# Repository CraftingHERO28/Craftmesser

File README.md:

# DIY Room Air Quality Monitor

I wanted to build a solid, reliable indoor air quality monitor to keep track of CO2 levels, temperature, and humidity in my room. A lot of cheap commercial monitors use estimated VOC sensors instead of actual optical sensors, so I decided to design my own board around an Arduino Nano and an NDIR MH-Z19B sensor.

## How it works & Hardware choices
The setup is built completely with through-hole (THT) components on socket headers so everything stays easy to solder and swap out if needed:

- **Arduino Nano v3.x** handling the logic.
- **MH-Z19B** for actual NDIR CO2 measurement.
- **DHT22 / AM2302** for temperature and humidity.
- **0.96" I2C OLED** for displaying live data.
- Decoupling caps (100nF ceramic & 100uF electrolytic) to smooth out voltage drops when the CO2 sensor warms up, plus a 10k pull-up for the DHT data line.

## Design notes & Things I ran into

- **Thermal Isolation:** The biggest challenge was keeping heat from the Arduino regulator and the CO2 sensor away from the temperature reading. I ended up placing the DHT22 at the far corner of the PCB away from major trace paths. 
- **Trace Routing:** I initially tried making decorative parallel power traces ("trace art"), but quickly realized it created routing clutter and unnecessary heat bridges toward the temp sensor. Going back to clean, single traces worked much better.
- **Edge Cuts:** I also experimented with slot cutouts on the PCB board outline (`Edge.Cuts`) for thermal isolation, but KiCad threw continuous DRC errors for open contours. Placing the sensor at the board edge using FR4's natural isolation turned out to be more than enough without messing with custom PCB millings.

## Total Cost
Total cost ended up around **€58 / ~$63 USD**, including component sourcing from Reichelt and getting 5 custom PCBs fabricated via JLCPCB (shipping included). Full component breakdown is available in the `BOM.csv` file.

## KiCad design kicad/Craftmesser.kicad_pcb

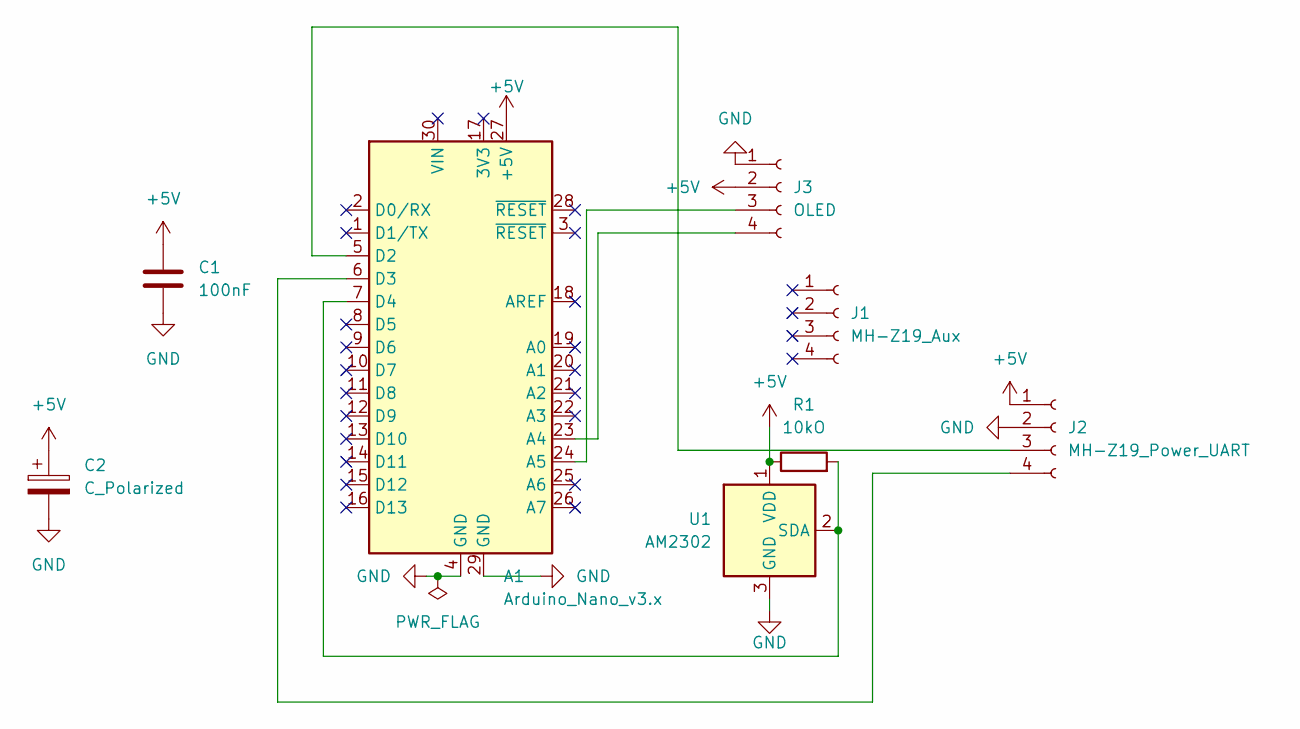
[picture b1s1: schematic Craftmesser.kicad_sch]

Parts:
A1: Arduino_Nano_v3.x; Arduino_Nano
C1: 100nF; C_Disc_D5.0mm_W2.5mm_P5.00mm
C2: C_Polarized; CP_Radial_D6.3mm_P2.50mm
J1: MH-Z19_Aux; PinHeader_1x04_P2.54mm_Vertical
J2: MH-Z19_Power_UART; PinHeader_1x04_P2.54mm_Vertical
J3: OLED; PinHeader_1x04_P2.54mm_Vertical
R1: 10kO; R_Axial_DIN0207_L6.3mm_D2.5mm_P7.62mm_Horizontal
U1: AM2302; ASAIR_AM2302_P2.54mm_Vertical

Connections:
+5V: A1.27 (+5V), C1.1, C2.1, J2.1, J3.2, R1.1, U1.1 (VDD)
GND: A1.4 (GND), A1.29 (GND), C1.2, C2.2, J2.2, J3.1, U1.3 (GND), U1.4 (GND)
unnamed: A1.23 (A4), J3.4
unnamed: A1.24 (A5), J3.3
unnamed: A1.5 (D2), J2.3
unnamed: A1.6 (D3), J2.4
unnamed: A1.7 (D4), R1.2, U1.2 (SDA)

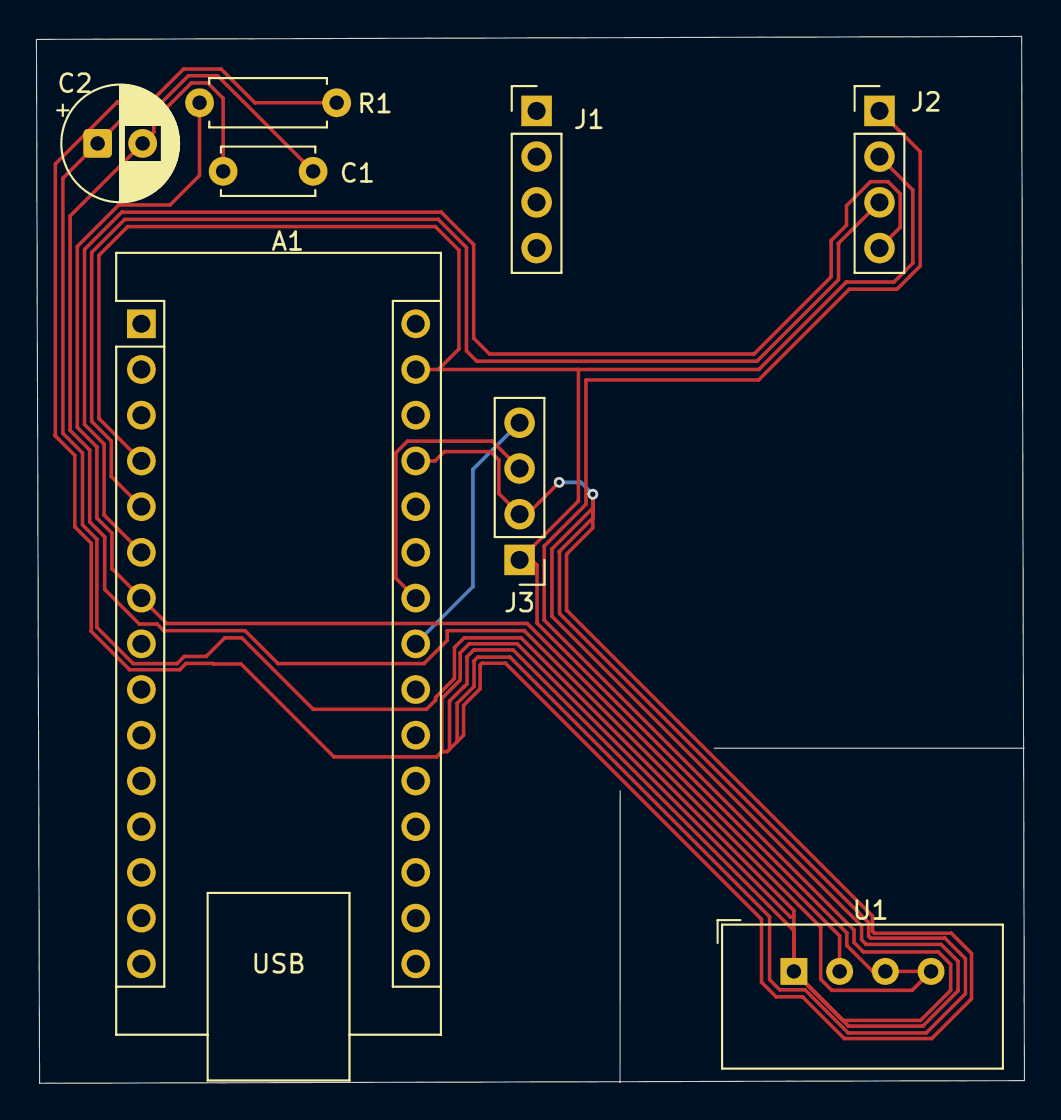
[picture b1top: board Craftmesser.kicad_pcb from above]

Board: 2 copper layers, 54.9 x 58.2 mm, 8 parts (0 on the bottom side), 7 nets.
